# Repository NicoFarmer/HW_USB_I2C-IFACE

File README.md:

# HW_USB_I2C-IFACE
Interface USB-I2C

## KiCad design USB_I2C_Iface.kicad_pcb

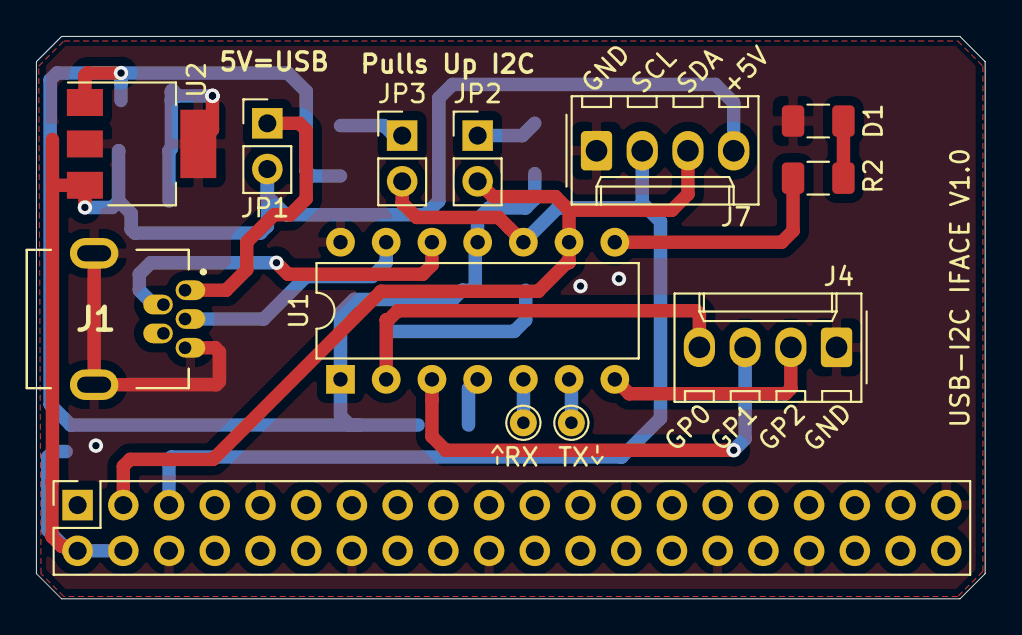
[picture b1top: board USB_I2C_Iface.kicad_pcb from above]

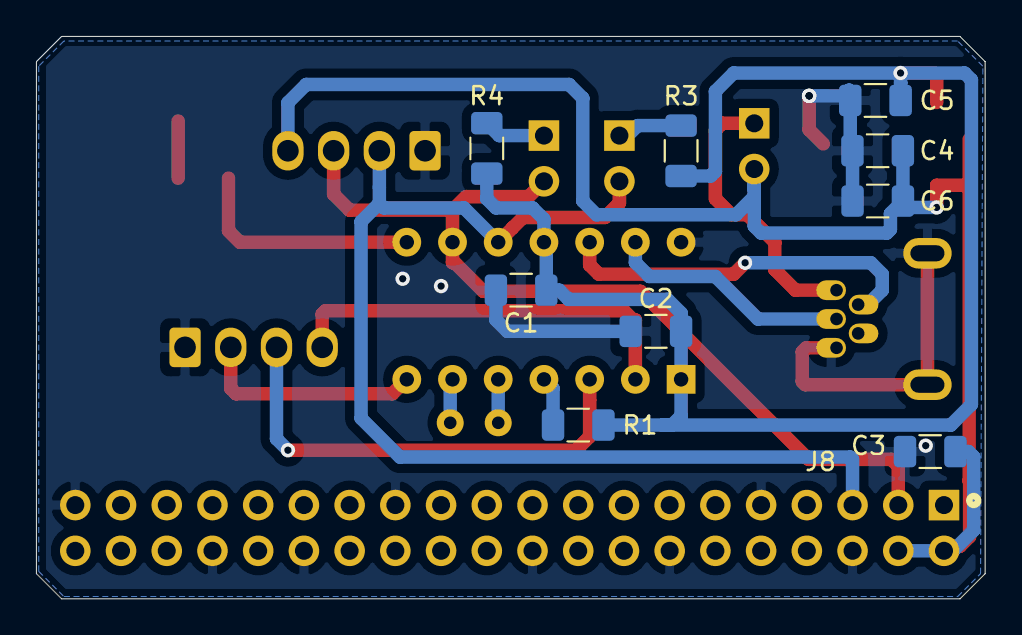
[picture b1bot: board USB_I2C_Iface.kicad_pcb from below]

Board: 2 copper layers, 52.7 x 31.2 mm, 22 parts (9 on the bottom side), 18 nets.

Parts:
C1: C; C_1206_3216Metric
C2, C6: 100n; C_1206_3216Metric
C3: 47u; C_1206_3216Metric
C4, C5: 1u; C_1206_3216Metric
D1: LED; C_1206_3216Metric
J1: USB_B_Mini; USB_Mini-B_Molex-548190519
J2, J3: Conn_01x01_Female; TestPoint_THTPad_D1.5mm_Drill0.7mm
J4, J7: Conn_01x04; Molex_KK-254_AE-6410-04A_1x04_P2.54mm_Vertical
J8: Raspberry_Pi_2_3; PinSocket_2x20_P2.54mm_Vertical
JP1, JP2, JP3: Jumper; PinHeader_1x02_P2.54mm_Vertical
R1: 10k; C_1206_3216Metric
R2: 470; C_1206_3216Metric
R3, R4: 4.7k; C_1206_3216Metric
U1: MCP2221; DIP-14_W7.62mm
U2: MCP1804x-3302xDB; SOT-223-3_TabPin2

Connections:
+3V3: C1.1, C2.2, C5.1, R1.1, R3.1, R4.1, U1.1, U1.11, U2.1
+5V: C3.1, C4.1, C6.1, J7.4, J8.2, J8.4, JP1.2, U2.3
/I2C_SCL: J7.2, J8.5, JP3.2, U1.10
/I2C_SDA: J7.3, J8.3, JP2.2, U1.9
/USB_D+: J1.3, U1.13
/USB_D-: J1.2, U1.12
GND: C1.2, C2.1, C3.2, C4.2, C5.2, C6.2, D1.1, J1.5, J1.6, J4.1, J7.1, J8.6, J8.9, J8.14, J8.20, J8.25, J8.30, J8.34, J8.39, U1.14, U2.2
unnamed: D1.2, R2.2
unnamed: J1.1, JP1.1
unnamed: J2.1, U1.5
unnamed: J3.1, U1.6
unnamed: J4.2, U1.7
unnamed: J4.3, U1.3
unnamed: J4.4, U1.2
unnamed: JP2.1, R4.2
unnamed: JP3.1, R3.2
unnamed: R1.2, U1.4
unnamed: R2.1, U1.8

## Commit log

2021-05-31 Version initiale du projet
2021-06-26 Ajout du pdf du schéma
